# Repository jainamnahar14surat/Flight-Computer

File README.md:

# Flight-Computer

A compact, custom-designed PCB (Printed Circuit Board) for a Flight Computer, aimed at aerospace applications like model rockets, UAVs, and experimental aircrafts. The design integrates essential sensors and microcontroller connections to provide reliable flight data acquisition and processing.

## Overview
The Flight Computer is powered by an STM32F405RG microcontroller, enabling real-time data acquisition from multiple environmental and motion sensors. It also supports wireless data transmission using the NRF24L01+PA radio module, and precise location tracking through the NEO-M9N GPS receiver. This project is currently at the prototype stage, aimed at validating the PCB layout, hardware interfacing, and initial sensor readings.

## Major Components

| Component | Description |
|:---|:---|
| **STM32F405RG** | High-performance ARM Cortex-M4 Microcontroller |
| **LM20BIM7** | Precision Temperature Sensor |
| **Si7020-A20** | Humidity Sensor with I²C Interface |
| **MPU6050** | 6-axis IMU (Accelerometer + Gyroscope) |
| **NEO-M9N** | High-Precision GPS Module |
| **NRF24L01+PA** | Long-Range Wireless Radio Module |

## Features

- **High-Speed Processing**: 168 MHz ARM Cortex-M4 with hardware floating-point unit (FPU).
- **Environmental Monitoring**: Temperature and humidity sensing for atmospheric studies.
- **Precise Navigation**: Real-time position and velocity data from GPS.
- **Wireless Telemetry**: Long-range data transmission using NRF24L01-PA module.
- **Motion Tracking**: 3-axis acceleration and 3-axis rotational velocity sensing.
- **Noise Filtering and Protection**: Power-line ferrite beads, fuses, and transient protection.
- **Modular Design**: Easy to add additional sensors or modules if needed.
- **Lightweight and Compact**: Optimized for minimal payload impact in flight applications.

## System Architecture

The Flight Computer follows a layered and modular system design, ensuring clear data flow and easy expandability. The architecture can be understood in three main layers:

### Sensor Layer
This layer is responsible for collecting environmental and motion data in real-time.
- **Temperature Sensor (LM20BIM7):**
    Measures ambient temperature and sends analog data to the STM32's ADC.

- **Humidity Sensor (Si7020-A20):**
    Captures precise humidity levels via the I2C interface.

- **IMU (MPU6050):**
    Provides 6-axis motion data (acceleration and gyroscope) over I2C communication.

### Processing Layer
The STM32F405RG acts as the central controller, performing the following:
- Reads sensor inputs (ADC, I2C, UART).
- Filters and processes sensor data.
- Combines multiple sensor readings for better situational awareness (sensor fusion).
- Prepares formatted data packets for transmission.

### Communication Layer
Handles external data transmission and navigation data retrieval.

- **GPS Module (NEO-M9N):**
    Interfaces over UART to provide real-time positioning information.

- **Wireless Radio (NRF24L01-PA):**
    Uses SPI communication to send collected flight data wirelessly to a ground receiver or base station.

## Repository Structure

| Folder/File	| Description |
|:---|:---|
| **assets**	| Datasheet of Components |
| **hardware_design/** |	Files related to PCB Design |
| **img/** |	PCB Image |
| **README.md** |	Project documentation |

## Applications

- High-Altitude Balloons
- Model Rocket Avionics
- Experimental UAV Flight Computers
- Remote Atmospheric Data Collection

## Future Enhancements

- Integration of SD card storage for redundant flight logging
- Addition of LoRaWAN communication for ultra-long range telemetry
- Redundant GPS modules for enhanced navigation reliability
- Automatic recovery and emergency shutdown systems

## License
This project is licensed under the [MIT License](LICENSE).

## Contact

Feel free to reach out for collaborations or just a friendly hello!

-   **Email:** naharjainam91@gmail.com
-   **LinkedIn:** https://www.linkedin.com/in/jainam-nahar-280292253
-   **GitHub:** https://github.com/jainamnahar14surat
-   **Website** https://jaina-portfolio.netlify.app/

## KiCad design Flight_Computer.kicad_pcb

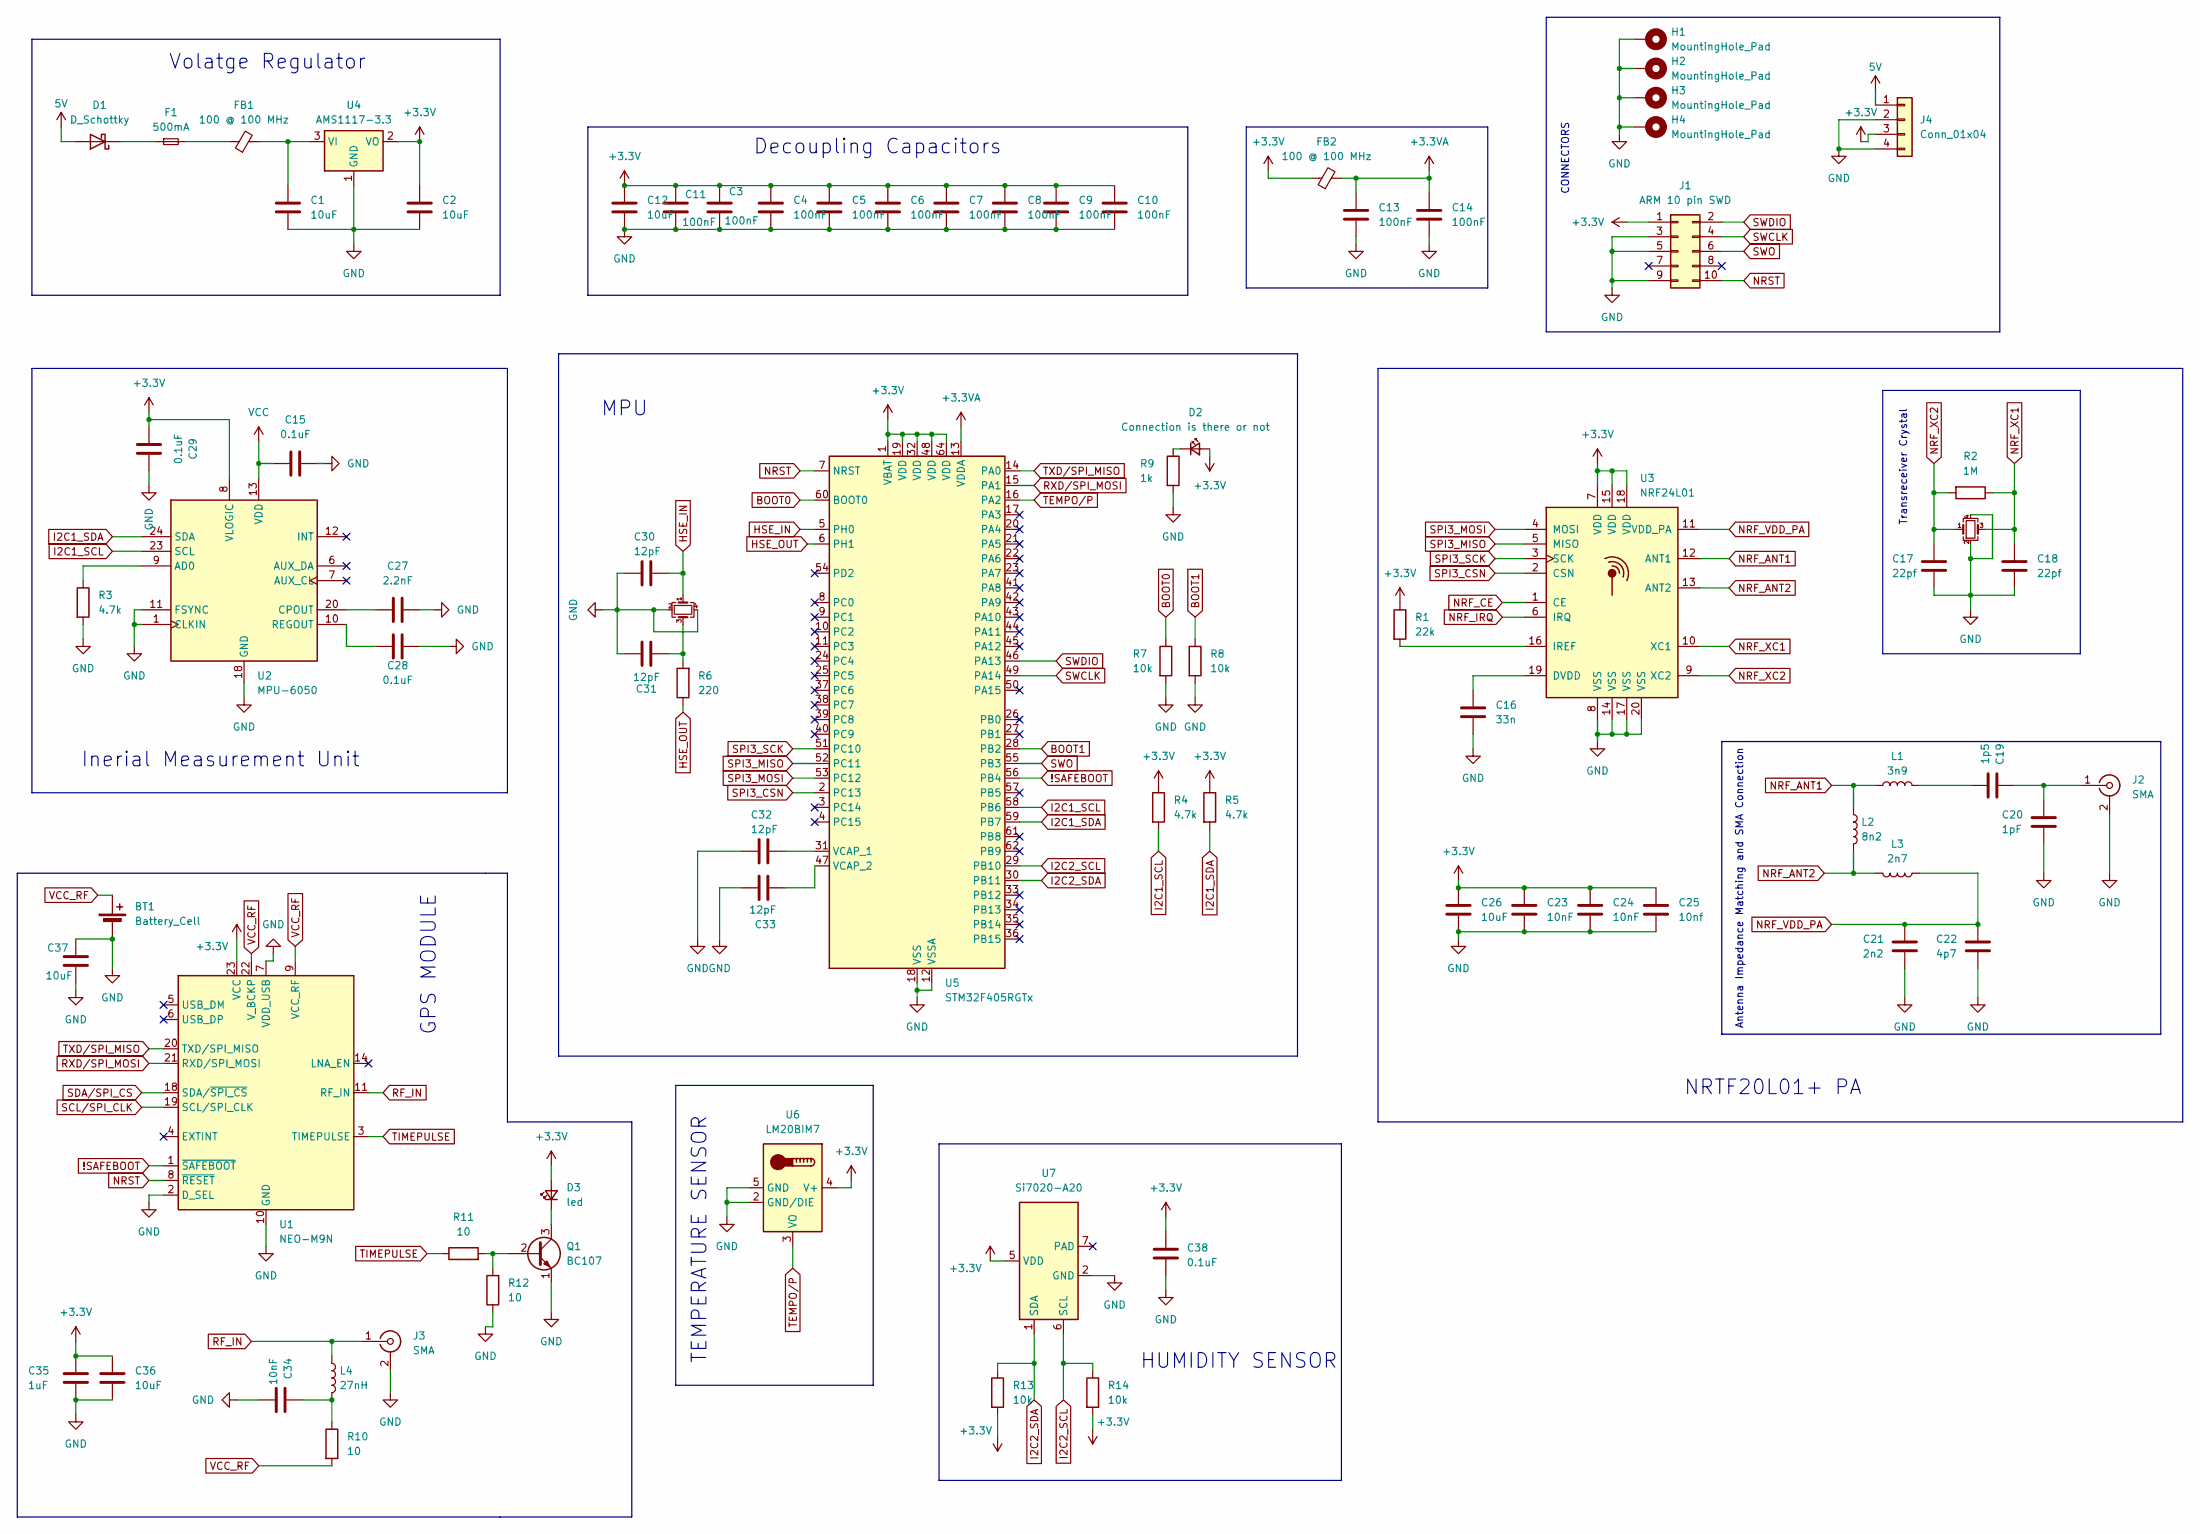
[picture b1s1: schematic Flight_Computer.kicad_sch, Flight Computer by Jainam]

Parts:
BT1: Battery_Cell; Panasonic_EVQPUJ_EVQPUA
C1, C12, C26, C36, C37: 10uF; C_0402_1005Metric
C2: 10uF; C_0805_2012Metric
C3, C4, C5, C6, C7, C8, C9, C10, C11, C13, C14: 100nF; C_0402_1005Metric
C15, C28, C29, C38: 0.1uF; C_0402_1005Metric
C16: 33n; C_0603_1608Metric
C17, C18: 22pf; C_0603_1608Metric
C19: 1p5; C_0402_1005Metric
C20: 1pF; C_0402_1005Metric
C21: 2n2; C_0402_1005Metric
C22: 4p7; C_0402_1005Metric
C23, C24, C34: 10nF; C_0402_1005Metric
C25: 10nf; C_0402_1005Metric
C27: 2.2nF; C_0402_1005Metric
C30, C31, C32, C33: 12pF; C_0402_1005Metric
C35: 1uF; C_0402_1005Metric
D1: D_Schottky; D_SOD-123
D2: Connection is there or not; LED_0603_1608Metric
D3: led; LED_0603_1608Metric
F1: 500mA; Fuse_1206_3216Metric
FB1, FB2: 100 @ 100 MHz; L_0805_2012Metric
H1, H2, H3, H4: MountingHole_Pad; MountingHole_4.3mm_M4_Pad_Via
J1: ARM 10 pin SWD; PinHeader_2x05_P1.27mm_Vertical
J2: SMA; BNC_Amphenol_031-5539_Vertical
J3: SMA; SMA_Samtec_SMA-J-P-X-ST-EM1_EdgeMount
J4: Conn_01x04; PinSocket_1x04_P1.27mm_Vertical
L1: 3n9; L_0402_1005Metric
L2: 8n2; L_0402_1005Metric
L3: 2n7; L_0402_1005Metric
L4: 27nH; L_0402_1005Metric
Q1: BC107; TO-39-3
R1: 22k; R_0603_1608Metric
R2: 1M; R_0402_1005Metric
R3, R4, R5: 4.7k; R_0805_2012Metric
R6: 220; R_2010_5025Metric
R7, R8, R13, R14: 10k; R_0402_1005Metric
R9: 1k; R_0603_1608Metric
R10, R11, R12: 10; R_0402_1005Metric
U1: NEO-M9N; ublox_NEO
U2: MPU-6050; InvenSense_QFN-24_4x4mm_P0.5mm
U3: NRF24L01; QFN-20-1EP_4x4mm_P0.5mm_EP2.5x2.5mm
U4: AMS1117-3.3; SOT-223-3_TabPin2
U5: STM32F405RGTx; LQFP-64_10x10mm_P0.5mm
U6: LM20BIM7; SOT-353_SC-70-5
U7: Si7020-A20; DFN-6-1EP_3x3mm_P1mm_EP1.5x2.4mm
Y1, Y2: Crystal_GND24_Small; Crystal_SMD_3225-4Pin_3.2x2.5mm

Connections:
5V: D1.2 (A), J4.1
!SAFEBOOT: U1.1 (~SAFEBOOT), U5.56 (PB4)
+3.3V: C2.1, C3.1, C4.1, C5.1, C6.1, C7.1, C8.1, C9.1, C10.1, C11.1, C12.1, C23.1, C24.1, C25.1, C26.1, C29.1, C35.2, C36.2, C38.2, D2.2 (A), D3.2 (A), FB2.1, J1.1, J4.3, R1.1, R4.1, R5.1, R13.2, R14.2, U1.23 (VCC), U2.8 (VLOGIC), U3.7 (VDD), U3.15 (VDD), U3.18 (VDD), U4.2 (VO), U5.1 (VBAT), U5.19 (VDD), U5.32 (VDD), U5.48 (VDD), U5.64 (VDD), U6.4 (V+), U7.5 (VDD)
+3.3VA: C13.1, C14.1, FB2.2, U5.13 (VDDA)
BOOT0: R7.1, U5.60 (BOOT0)
BOOT1: R8.1, U5.28 (PB2)
GND: BT1.2 (-), C1.2, C2.2, C3.2, C4.2, C5.2, C6.2, C7.2, C8.2, C9.2, C10.2, C11.2, C12.2, C13.2, C14.2, C15.2, C16.2, C17.2, C18.2, C20.2, C21.2, C22.2, C23.2, C24.2, C25.2, C26.2, C27.2, C28.1, C29.2, C30.2, C31.2, C32.2, C33.1, C34.2, C35.1, C36.1, C37.1, C37.2, C38.1, H1.1, H2.1, H3.1, H4.1, J1.3, J1.5, J1.9, J2.2 (Ext), J3.2 (Ext), J4.2, J4.4, Q1.1 (E), R3.2, R7.2, R8.2, R9.2, R12.1, U1.2 (D_SEL), U1.7 (VDD_USB), U1.10 (GND), U1.12 (GND), U1.13 (GND), U1.24 (GND), U2.1 (CLKIN), U2.11 (FSYNC), U2.18 (GND), U3.8 (VSS), U3.14 (VSS), U3.17 (VSS), U3.20 (VSS), U4.1 (GND), U5.12 (VSSA), U5.18 (VSS), U5.63 (VSS), U6.2 (GND/DIE), U6.5 (GND), U7.2 (GND), Y1.2, Y1.4, Y2.2, Y2.4
HSE_IN: C30.1, U5.5 (PH0), Y1.1
HSE_OUT: R6.1, U5.6 (PH1)
I2C1_SCL: R4.2, U2.23 (SCL), U5.58 (PB6)
I2C1_SDA: R5.2, U2.24 (SDA), U5.59 (PB7)
I2C2_SCL: R14.1, U5.29 (PB10), U7.6 (SCL)
I2C2_SDA: R13.1, U5.30 (PB11), U7.1 (SDA)
NRF_ANT1: L1.1, L2.1, U3.12 (ANT1)
NRF_ANT2: L2.2, L3.2, U3.13 (ANT2)
NRF_CE: U3.1 (CE)
NRF_IRQ: U3.6 (IRQ)
NRF_VDD_PA: C21.1, C22.1, L3.1, U3.11 (VDD_PA)
NRF_XC1: C18.1, R2.1, U3.10 (XC1), Y2.3
NRF_XC2: C17.1, R2.2, U3.9 (XC2), Y2.1
NRST: J1.10, U1.8 (~RESET), U5.7 (NRST)
unnamed: C19.2, L1.2
unnamed: C31.1, R6.2, Y1.3
unnamed: C34.1, L4.2, R10.1
unnamed: D1.1 (K), F1.1
unnamed: D2.1 (K), R9.1
unnamed: D3.1 (K), Q1.3 (C)
unnamed: F1.2, FB1.1
unnamed: C19.1, C20.1, J2.1 (In)
unnamed: Q1.2 (B), R11.2, R12.2
unnamed: R3.1, U2.9 (AD0)
unnamed: C27.1, U2.20 (CPOUT)
unnamed: C28.2, U2.10 (REGOUT)
unnamed: C16.1, U3.19 (DVDD)
unnamed: R1.2, U3.16 (IREF)
unnamed: C1.1, FB1.2, U4.3 (VI)
unnamed: C32.1, U5.31 (VCAP_1)
unnamed: C33.2, U5.47 (VCAP_2)
RF_IN: J3.1 (In), L4.1, U1.11 (RF_IN)
RXD/SPI_MOSI: U1.21 (RXD/SPI_MOSI), U5.15 (PA1)
SCL/SPI_CLK: U1.19 (SCL/SPI_CLK)
SDA/SPI_CS: U1.18 (SDA/~SPI_CS)
SPI3_CSN: U3.2 (CSN), U5.2 (PC13)
SPI3_MISO: U3.5 (MISO), U5.52 (PC11)
SPI3_MOSI: U3.4 (MOSI), U5.53 (PC12)
SPI3_SCK: U3.3 (SCK), U5.51 (PC10)
SWCLK: J1.4, U5.49 (PA14)
SWDIO: J1.2, U5.46 (PA13)
SWO: J1.6, U5.55 (PB3)
TEMPO/P: U5.16 (PA2), U6.3 (VO)
TIMEPULSE: R11.1, U1.3 (TIMEPULSE)
TXD/SPI_MISO: U1.20 (TXD/SPI_MISO), U5.14 (PA0)
VCC: C15.1, U2.13 (VDD)
VCC_RF: BT1.1 (+), R10.2, U1.9 (VCC_RF), U1.22 (V_BCKP)

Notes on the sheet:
NRTF20L01+ PA
MPU
TEMPERATURE SENSOR
Volatge Regulator
Inerial Measurement Unit
Decoupling Capacitors
GPS MODULE
CONNECTORS
Antenna Impedance Matching and SMA Connection
HUMIDITY SENSOR
Transreceiver Crystal

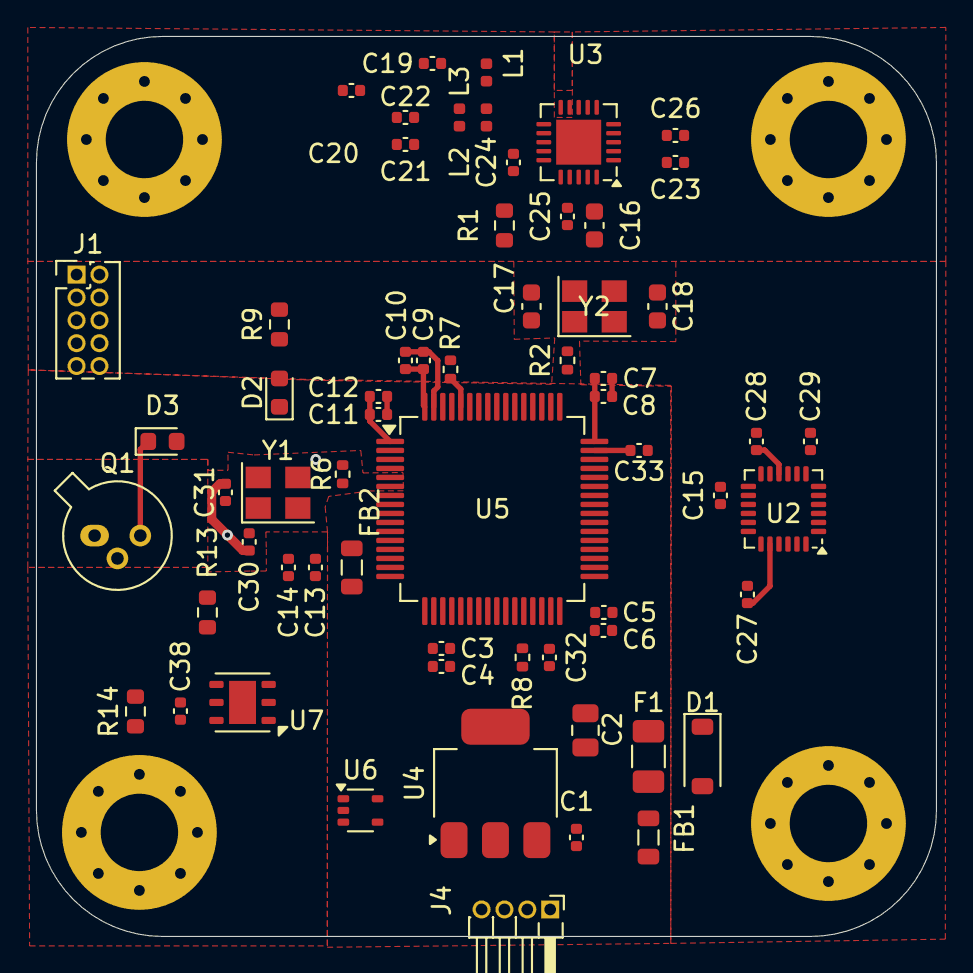
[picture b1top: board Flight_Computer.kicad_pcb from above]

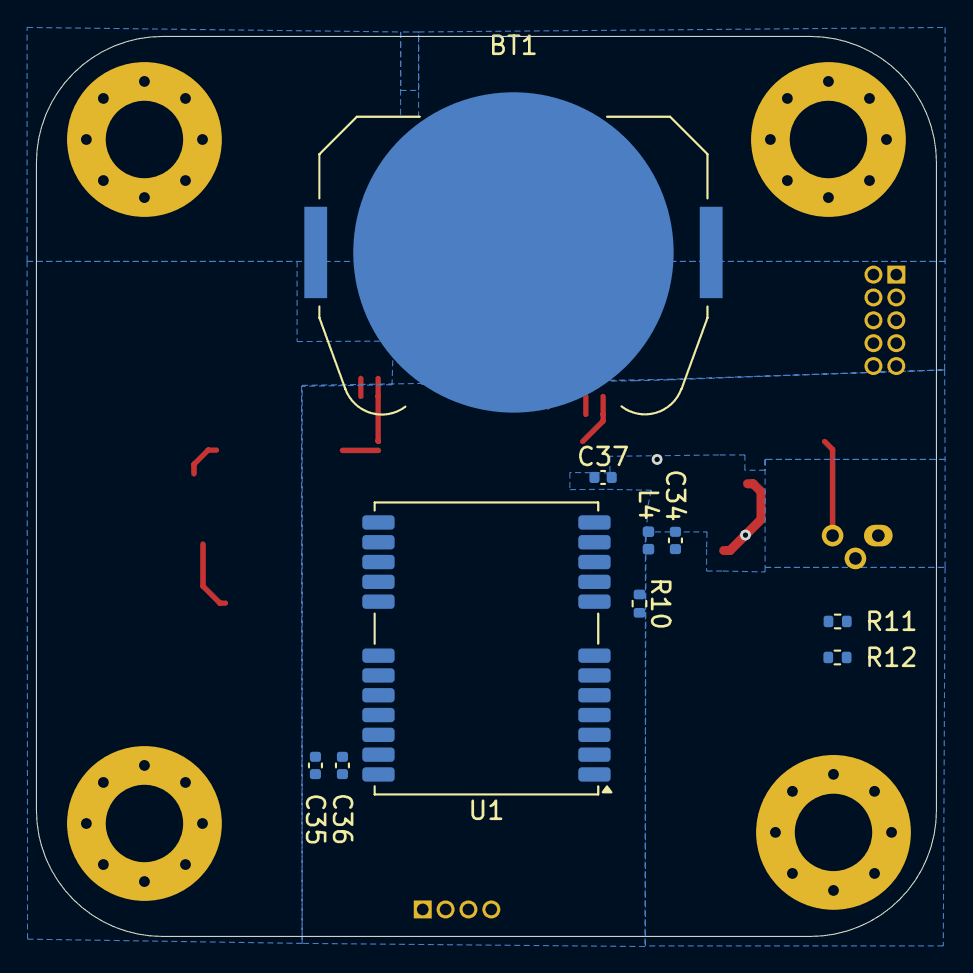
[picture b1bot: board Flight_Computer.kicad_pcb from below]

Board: 6 copper layers, 50.0 x 50.0 mm, 76 parts (10 on the bottom side), 49 nets.

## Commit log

2024-08-08 Create assets
2024-08-08 documents
2024-08-08 second commit
2025-04-26 Create LICENSE
2025-04-26 restructure file
2025-04-26 update assests
2026-02-07 Add contact section to README
    Added contact information for collaborations and inquiries.
